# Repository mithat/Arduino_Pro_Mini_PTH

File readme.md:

Arduino_Pro_Mini_PTH
====================

Crazy stupid experiment to see how close you can get to an 
[Arduino Pro Mini](http://arduino.cc/en/Main/arduinoBoardProMini) using 
through hole parts.

Made with [KiCad](http://www.kicad-pcb.org/), which is [free and open source software](http://en.wikipedia.org/wiki/Free_and_open-source_software).
No raptors were touched in the making of this board.

No, I haven't built it (yet?).

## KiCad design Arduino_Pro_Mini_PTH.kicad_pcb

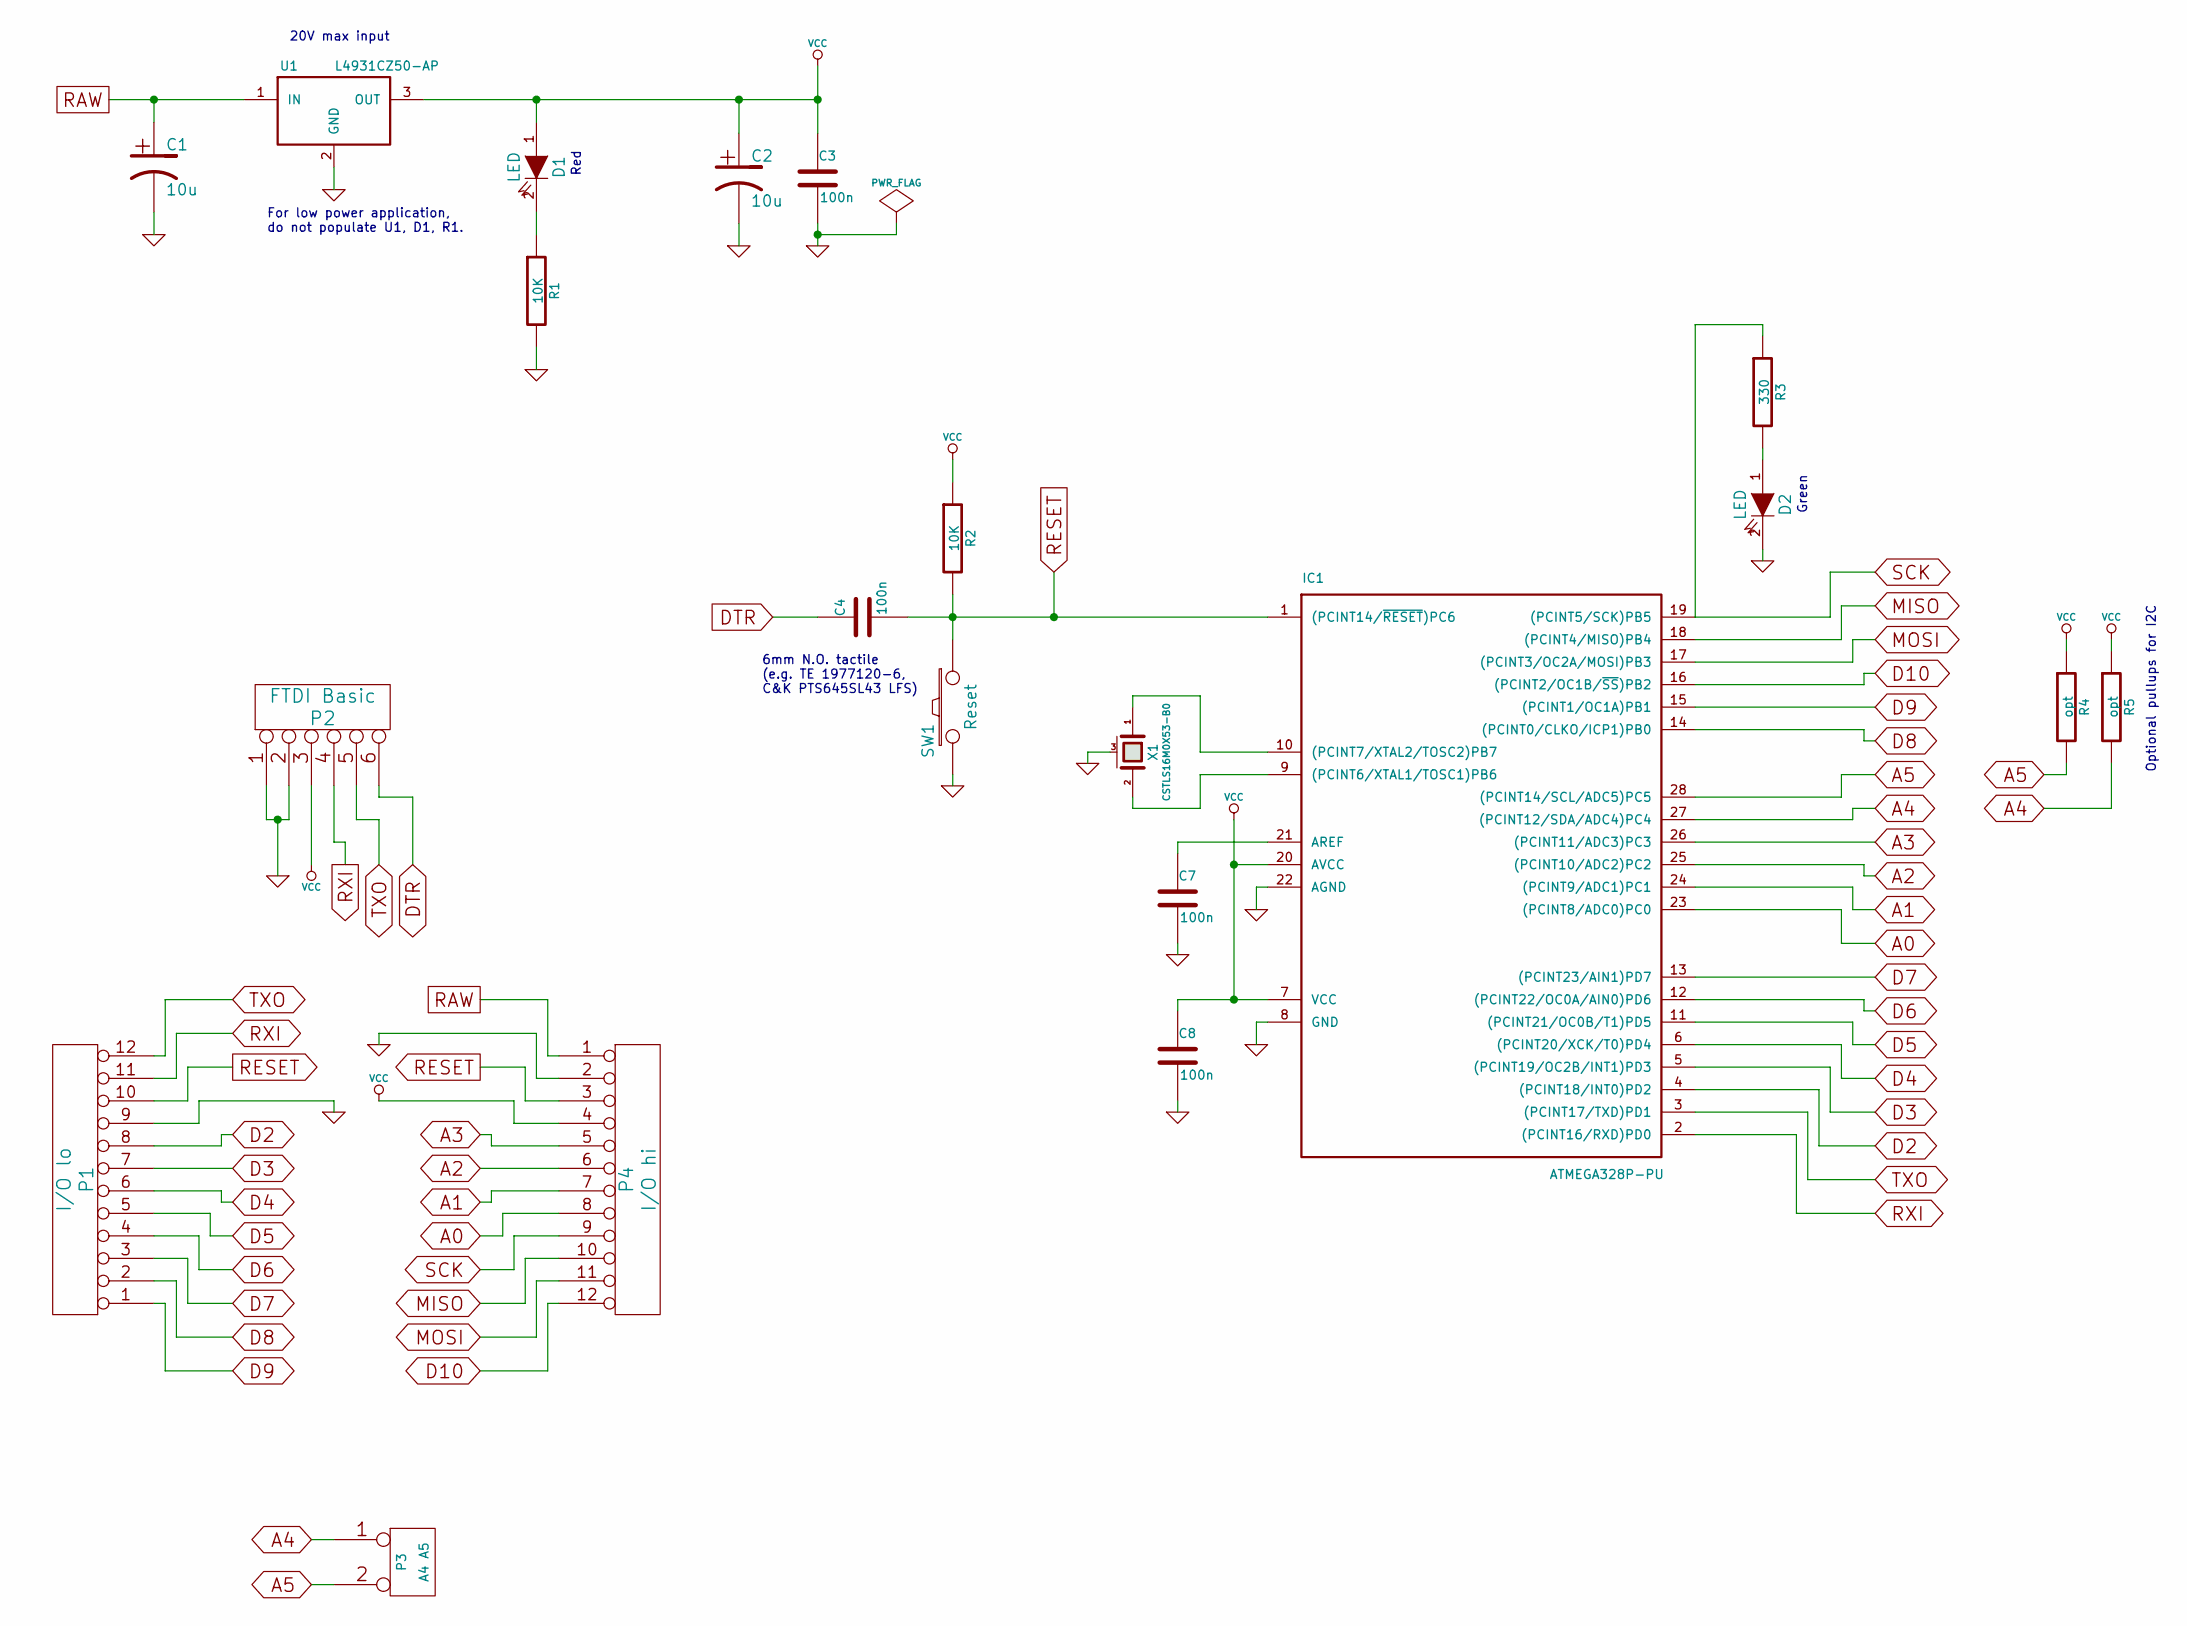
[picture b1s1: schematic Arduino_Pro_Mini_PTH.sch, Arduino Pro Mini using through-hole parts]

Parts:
C1, C2: 10u; mfk-CRP_5.0_2.0_0.5
C3, C4, C7, C8: 100n; mfk-C_4.0_2.5_2.5_0.5
D1, D2: LED; LED-3MM
IC1: ATMEGA328P-PU; mfk-DIP-28_300_rnd
P1: I/O lo; mfk-SIL-12
P2: FTDI Basic; mfk-SIL-6
P3: A4 A5; mfk-SIL-2
P4: I/O hi; mfk-SIL-12
R1, R2: 10K; mfk-R_0.25W_RN55_vert
R3: 330; mfk-R_0.25W_RN55_vert
R4, R5: opt; mfk-R_0.25W_RN55_vert
SW1: Reset; mfk-SW_PUSH_6MM
U1: L4931CZ50-AP; mfk-TO-92_f321
X1: CSTLS16M0X53-B0; mfk-Murata-CSTLS_X

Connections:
A0: IC1.23 ((PCINT8/ADC0)PC0), P4.8
A1: IC1.24 ((PCINT9/ADC1)PC1), P4.7
A2: IC1.25 ((PCINT10/ADC2)PC2), P4.6
A3: IC1.26 ((PCINT11/ADC3)PC3), P4.5
A4: IC1.27 ((PCINT12/SDA/ADC4)PC4), P3.1, R5.2
A5: IC1.28 ((PCINT14/SCL/ADC5)PC5), P3.2 (PM), R4.2
D2: IC1.4 ((PCINT18/INT0)PD2), P1.8
D3: IC1.5 ((PCINT19/OC2B/INT1)PD3), P1.7
D4: IC1.6 ((PCINT20/XCK/T0)PD4), P1.6
D5: IC1.11 ((PCINT21/OC0B/T1)PD5), P1.5
D6: IC1.12 ((PCINT22/OC0A/AIN0)PD6), P1.4
D7: IC1.13 ((PCINT23/AIN1)PD7), P1.3
D8: IC1.14 ((PCINT0/CLKO/ICP1)PB0), P1.2
D9: IC1.15 ((PCINT1/OC1A)PB1), P1.1
D10: IC1.16 ((PCINT2/OC1B/~SS~)PB2), P4.12
DTR: C4.1, P2.6
GND: C1.2, C2.2, C3.2, C7.2, C8.2, D2.2 (K), IC1.8 (GND), IC1.22 (AGND), P1.9, P2.1, P2.2, P4.2, R1.2, SW1.2, U1.2 (GND), X1.3 (case)
MISO: IC1.18 ((PCINT4/MISO)PB4), P4.10
MOSI: IC1.17 ((PCINT3/OC2A/MOSI)PB3), P4.11
unnamed: D2.1 (A), R3.2
unnamed: D1.2 (K), R1.1
unnamed: C7.1, IC1.21 (AREF)
unnamed: IC1.10 ((PCINT7/XTAL2/TOSC2)PB7), X1.1
unnamed: IC1.9 ((PCINT6/XTAL1/TOSC1)PB6), X1.2
RAW: C1.1, P4.1, U1.1 (IN)
RESET: C4.2, IC1.1 ((PCINT14/~RESET~)PC6), P1.10, P4.3, R2.2, SW1.1
RXI: IC1.2 ((PCINT16/RXD)PD0), P1.11, P2.4
SCK: IC1.19 ((PCINT5/SCK)PB5), P4.9, R3.1
TXO: IC1.3 ((PCINT17/TXD)PD1), P1.12, P2.5
VCC: C2.1, C3.1, C8.1, D1.1 (A), IC1.7 (VCC), IC1.20 (AVCC), P2.3, P4.4, R2.1, R4.1, R5.1, U1.3 (OUT)

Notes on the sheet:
Green
Optional pullups for I2C
Red
20V max input
6mm N.O. tactile (e.g. TE 1977120-6, C&K PTS645SL43 LFS)
For low power application, do not populate U1, D1, R1.

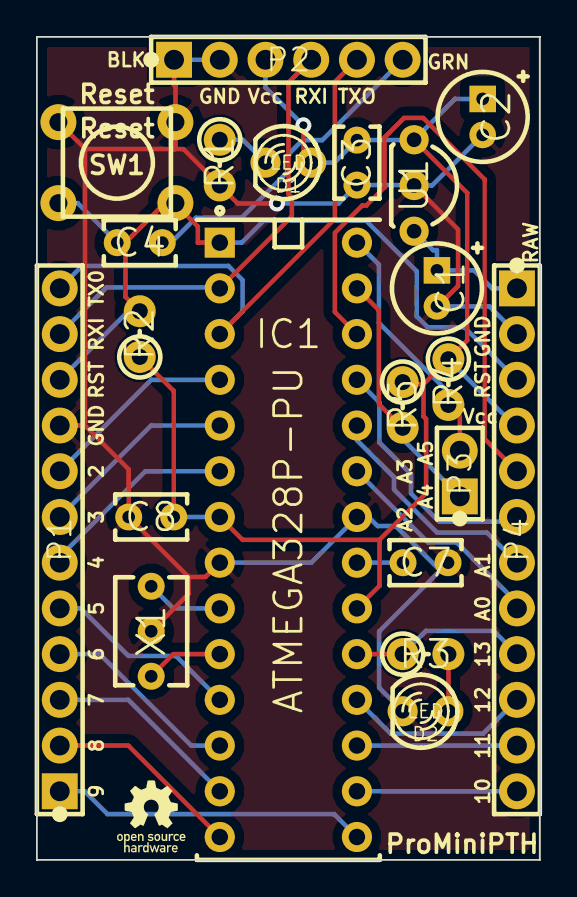
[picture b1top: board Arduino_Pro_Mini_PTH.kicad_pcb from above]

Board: 2 copper layers, 27.9 x 45.7 mm, 22 parts (0 on the bottom side), 30 nets.

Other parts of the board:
VAL: REF; oshw-logo-150mil-FSilk

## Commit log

2015-03-25 Initial commit.
2015-03-26 Schematic complete.
2015-03-26 Module associations.
2015-03-26 Routed.
2015-03-26 Routed. Flooded. Silkscreen.
2015-03-26 Fixed mislabeled A1. Moves OSH logo.
2015-03-26 Schematic placement tweaks.
2015-03-26 Changed reference to KiCad in readme.
2015-03-26 readme syntax error fix.

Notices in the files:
Arduino_Pro_Mini_PTH.kicad_pcb:
Creative Commons Attribution Share Alike 3.0 License
